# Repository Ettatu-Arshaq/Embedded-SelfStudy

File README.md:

# 🚀 Embedded Systems Self-Study Journey

**Author:** Muhammad Arshaq (Ettatu-Arshaq)
**Goal:** Become job-ready for Embedded Systems roles by **December 2025** through self-study and hands-on projects.

---

## 📅 Roadmap Overview

This repository documents my entire **Embedded Systems self-study path** — from C programming to IoT and RTOS — built phase by phase with practical examples and mini-projects.

---

## 📂 Phase 1: C Programming & Linux Fundamentals

* ✅ Variables, loops, functions, arrays, strings
* ✅ Structures, file handling, pointers, DMA

### 📂 Workouts (Practice Programs)

Located in [`Phase1_C/Workouts/C`](./Phase1_C/Workouts/C)

#### 🔗 Quick Links

* **Matrix Operations**

  * [Add two matrices](./Phase1_C/Workouts/C/Add_matrix.c)
  * [Add two matrices (function-based)](./Phase1_C/Workouts/C/Add_matrix_fn.c)
* **Arrays & Statistics**

  * [Average of Array](./Phase1_C/Workouts/C/Avg%20of%20Array_1_9-6-25.c)
  * [Largest Element in Array](./Phase1_C/Workouts/C/Largest_Element_inarray.c)
  * [Standard Deviation](./Phase1_C/Workouts/C/Standard_Deviation.c)
* **Strings**

  * [Count String Function](./Phase1_C/Workouts/C/Count_stringfn.c)
  * [Character Frequency](./Phase1_C/Workouts/C/char_freq.c)
  * [Remove Substring](./Phase1_C/Workouts/C/strremove.c)
  * [Reverse String](./Phase1_C/Workouts/C/strrev.c)
  * [String Sort Hierarchy](./Phase1_C/Workouts/C/strsorthirerarcy.c)
* **File Handling**

  * [File Handling Basics](./Phase1_C/Workouts/C/File.c)
  * [Binary File Write](./Phase1_C/Workouts/C/File_bin_wr.c)
  * [Text → Binary: Entry.txt](./Phase1_C/Workouts/C/txtorbin/Entry.txt)
  * [Text → Binary: Student.txt](./Phase1_C/Workouts/C/txtorbin/Student.txt)
* **Pointers & Memory**

  * [Dynamic Memory Example](./Phase1_C/Workouts/C/memory.c)
  * [Pointer Demo](./Phase1_C/Workouts/C/pointer.c)
  * [Pointer Basics](./Phase1_C/Workouts/C/pointer_basics.c)
  * [Pointer Arithmetic](./Phase1_C/Workouts/C/pointer_arthematic.c)
  * [Print Address](./Phase1_C/Workouts/C/print_adress.c)
* **Misc Examples**

  * [Example Program](./Phase1_C/Workouts/C/example.c)
  * [Temp Runner](./Phase1_C/Workouts/C/tempCodeRunnerFile.c)
  * [Extern Keyword Example](./Phase1_C/Workouts/C/ext.c)
  * [Main Function Demo](./Phase1_C/Workouts/C/main.c)

---

### 📂 Mini Projects

* [`Student Record Manager`](./Phase1_C/StudentManager)

  * C program using structures and binary file handling
  * Add, search, delete, and view student records
  * Demonstrates persistence with `.bin` files

* [`Student Manager Dynamic`](./Phase1_C/StudentManager/Student_Dynamic.c)

  * Enhanced Student Manager using dynamic memory allocation

* [`Bitwise Demo`](./Phase1_C/Bitwise_Demo)

  * Practice on bitwise operators and manipulation in C
  * Includes [Bitwise_Demo.c](./Phase1_C/Bitwise_Demo/Bitwise_Demo.c) with explanations

* [`LED Blinker`](./Phase1_C/LED_Blinker)

  * A simple LED blinking project (Code::Blocks project)
  * Includes [main.c](./Phase1_C/LED_Blinker/main.c), configs, and layout files

---

## 📂 Phase 2: Microcontroller Programming (PIC16F1519)

Located in [`Phase2_MC_PIC16F1519`](./Phase2_MC_PIC16F1519)

### 📁 Projects

* [LED 7-Segment Display](./Phase2_MC_PIC16F1519/LED_7Segment.X)
* [Multi-LED Patterns (GPIO only)](./Phase2_MC_PIC16F1519/Multi-LED%20Patterns%20%28GPIO%20only%29.X)
* [Timer Tick 2 LED](./Phase2_MC_PIC16F1519/Timer_tick_2_LED.X)

### 📂 Workouts

* [ADC LED Blink](./Phase2_MC_PIC16F1519/Workouts/ADC_LED_BLINK.X)
* [ADC Potentiometer Poll](./Phase2_MC_PIC16F1519/Workouts/ADC_Potentiometer_poll.X)
* [ADC Reader UART Select](./Phase2_MC_PIC16F1519/Workouts/ADC_READER_UART_SELECT.X)
* [Blink LED](./Phase2_MC_PIC16F1519/Workouts/BLINK_led.X)
* [Counter using Timer](./Phase2_MC_PIC16F1519/Workouts/Counter/Counter_using_timer.X)
* [EEPROM PIC](./Phase2_MC_PIC16F1519/Workouts/EEPROM_PIC.X)
* [EEPROM UART PIC](./Phase2_MC_PIC16F1519/Workouts/EEPROM_UART_PIC.X)
* [LED GPIO Trigger](./Phase2_MC_PIC16F1519/Workouts/LED_GPIO_TRIG.X)
* [PIC SPI Master](./Phase2_MC_PIC16F1519/Workouts/PIC_SPI.X)
* [PIC SPI Slave](./Phase2_MC_PIC16F1519/Workouts/PIC_SPI_SLAVE.X)
* [PWM Hardware](./Phase2_MC_PIC16F1519/Workouts/PWM.X)
* [PWM Software](./Phase2_MC_PIC16F1519/Workouts/PWM_soft.X)
* [Timer0](./Phase2_MC_PIC16F1519/Workouts/Time0)
* [Timer1](./Phase2_MC_PIC16F1519/Workouts/Timer1.X)
* [Timer2](./Phase2_MC_PIC16F1519/Workouts/Timer2.X)
* [UART Rx Program](./Phase2_MC_PIC16F1519/Workouts/UART_Rx_PGM.X)

---

## 📂 Phase 3: STM32 & RTOS (In Progress)

Located in [`Phase3_STM32`](./Phase3_STM32)

### 🧠 Topics Covered

* Bare-metal driver development (GPIO, RCC, Registers)
* STM32 architecture (ARM Cortex-M)
* Interrupts, Timers, PWM
* UART, SPI communication
* Introduction to FreeRTOS (Tasks, Queues, Semaphores)

---

### 📁 Projects

* [FreeRTOS Button Event System](./Phase3_STM32/RTOS_MiniProject/)
* [STM32 Smart Control System)](./Phase3_STM32/UART_Based_Smart_Control_System_ISR/)

---

### 📂 Workouts

* [UART Based Smart Control System](./Phase3_STM32/Workouts/UART_Based_Smart_Control_System/)
* [SYSTICK](./Phase3_STM32/Workouts/SYSTICK_/)
* [TIM2 Interrupt](./Phase3_STM32/Workouts/TIM2_INT/)
* [TIM2 LED Blink](./Phase3_STM32/Workouts/TIM2_LEDBlink/)
* [RTOS Soft Timer](./Phase3_STM32/Workouts/RTOS_SoftTimer/)
* [SYSClock Check](./Phase3_STM32/Workouts/SYSClock_Check/)
* [RTOS Semaphore](./Phase3_STM32/Workouts/RTOS_Semaphore/)
* [RTOS Queue TxRx](./Phase3_STM32/Workouts/RTOS_Queue_TxRx/)
* [RTOS Queue ISR](./Phase3_STM32/Workouts/RTOS_Queue_ISR/)
* [RTOS Queue](./Phase3_STM32/Workouts/RTOS_Queue/)
* [RTOS Mutex](./Phase3_STM32/Workouts/RTOS_Mutex/)
* [RTOS LED](./Phase3_STM32/Workouts/RTOS_LED/)
* [RTOS Heap](./Phase3_STM32/Workouts/RTOS_Heap/)
* [LED Blink Pattern](./Phase3_STM32/Workouts/LED_Blink_Patt/)
* [PWM](./Phase3_STM32/Workouts/PWM/)
* [EXTI](./Phase3_STM32/Workouts/EXTI/)
* [EXTI Debounce](./Phase3_STM32/Workouts/EXTI-debounce/)
* [LED Blink](./Phase3_STM32/Workouts/LED_Blink/)
* [LED Blink CMSIS](./Phase3_STM32/Workouts/LED_Blink_CMSIS/)
* [ADC DMA Channel](./Phase3_STM32/Workouts/ADC+dma_Ch/)
* [Clock 1](./Phase3_STM32/Workouts/Clock_1/)
* [Clock HSE PLL](./Phase3_STM32/Workouts/Clock_HSE_PLL/)
* [Clock PLL Speed](./Phase3_STM32/Workouts/Clock_pll_speed/)
* [ADC](./Phase3_STM32/Workouts/ADC/)
* [ADC DMA](./Phase3_STM32/Workouts/ADC+dma/)
---

## 📂 Phase 4: IoT & Cloud Integration *(Upcoming)*

* ESP32 with MQTT & Blynk
* Cloud dashboard (Firebase)

---

## 📂 Phase 5: Final Project & Job Preparation *(Upcoming)*

* Internship-level embedded project
* Resume, GitHub portfolio, LinkedIn updates

---

## 📦 Repository Structure

Embedded-SelfStudy/
├── Phase1_C/
│ ├── Workouts/
│ │ └── C/ # Practice programs
│ ├── Bitwise_Demo/ # Bitwise operator practice
│ ├── StudentManager/ # Mini Projects
│ └── LED_Blinker/ # LED Blinker project
├── Phase2_MC_PIC16F1519/
│ ├── Workouts/
│ ├── LED_7Segment.X/
│ └── Multi-LED Patterns (GPIO only).X/
└── ...
├── Phase3_RTOS/ # Will be added later
└── ...

---

## 🛠 Tools & Platforms

* **Languages:** C, Python
* **Boards:** ESP32, STM32 Nucleo, Raspberry Pi
* **IDE/Tools:** Arduino IDE, PlatformIO, STM32CubeIDE, Proteus, Code::Blocks
* **OS:** Windows + Linux basics

---

## 📢 Connect

* [GitHub Profile](https://github.com/Ettatu-Arshaq)
* [LinkedIn](https://www.linkedin.com/in/muhammad-arshaq-0b7455237/)

---

📅 **Started:** August 2025
💡 **Goal:** Complete all phases & projects by **December 2025**

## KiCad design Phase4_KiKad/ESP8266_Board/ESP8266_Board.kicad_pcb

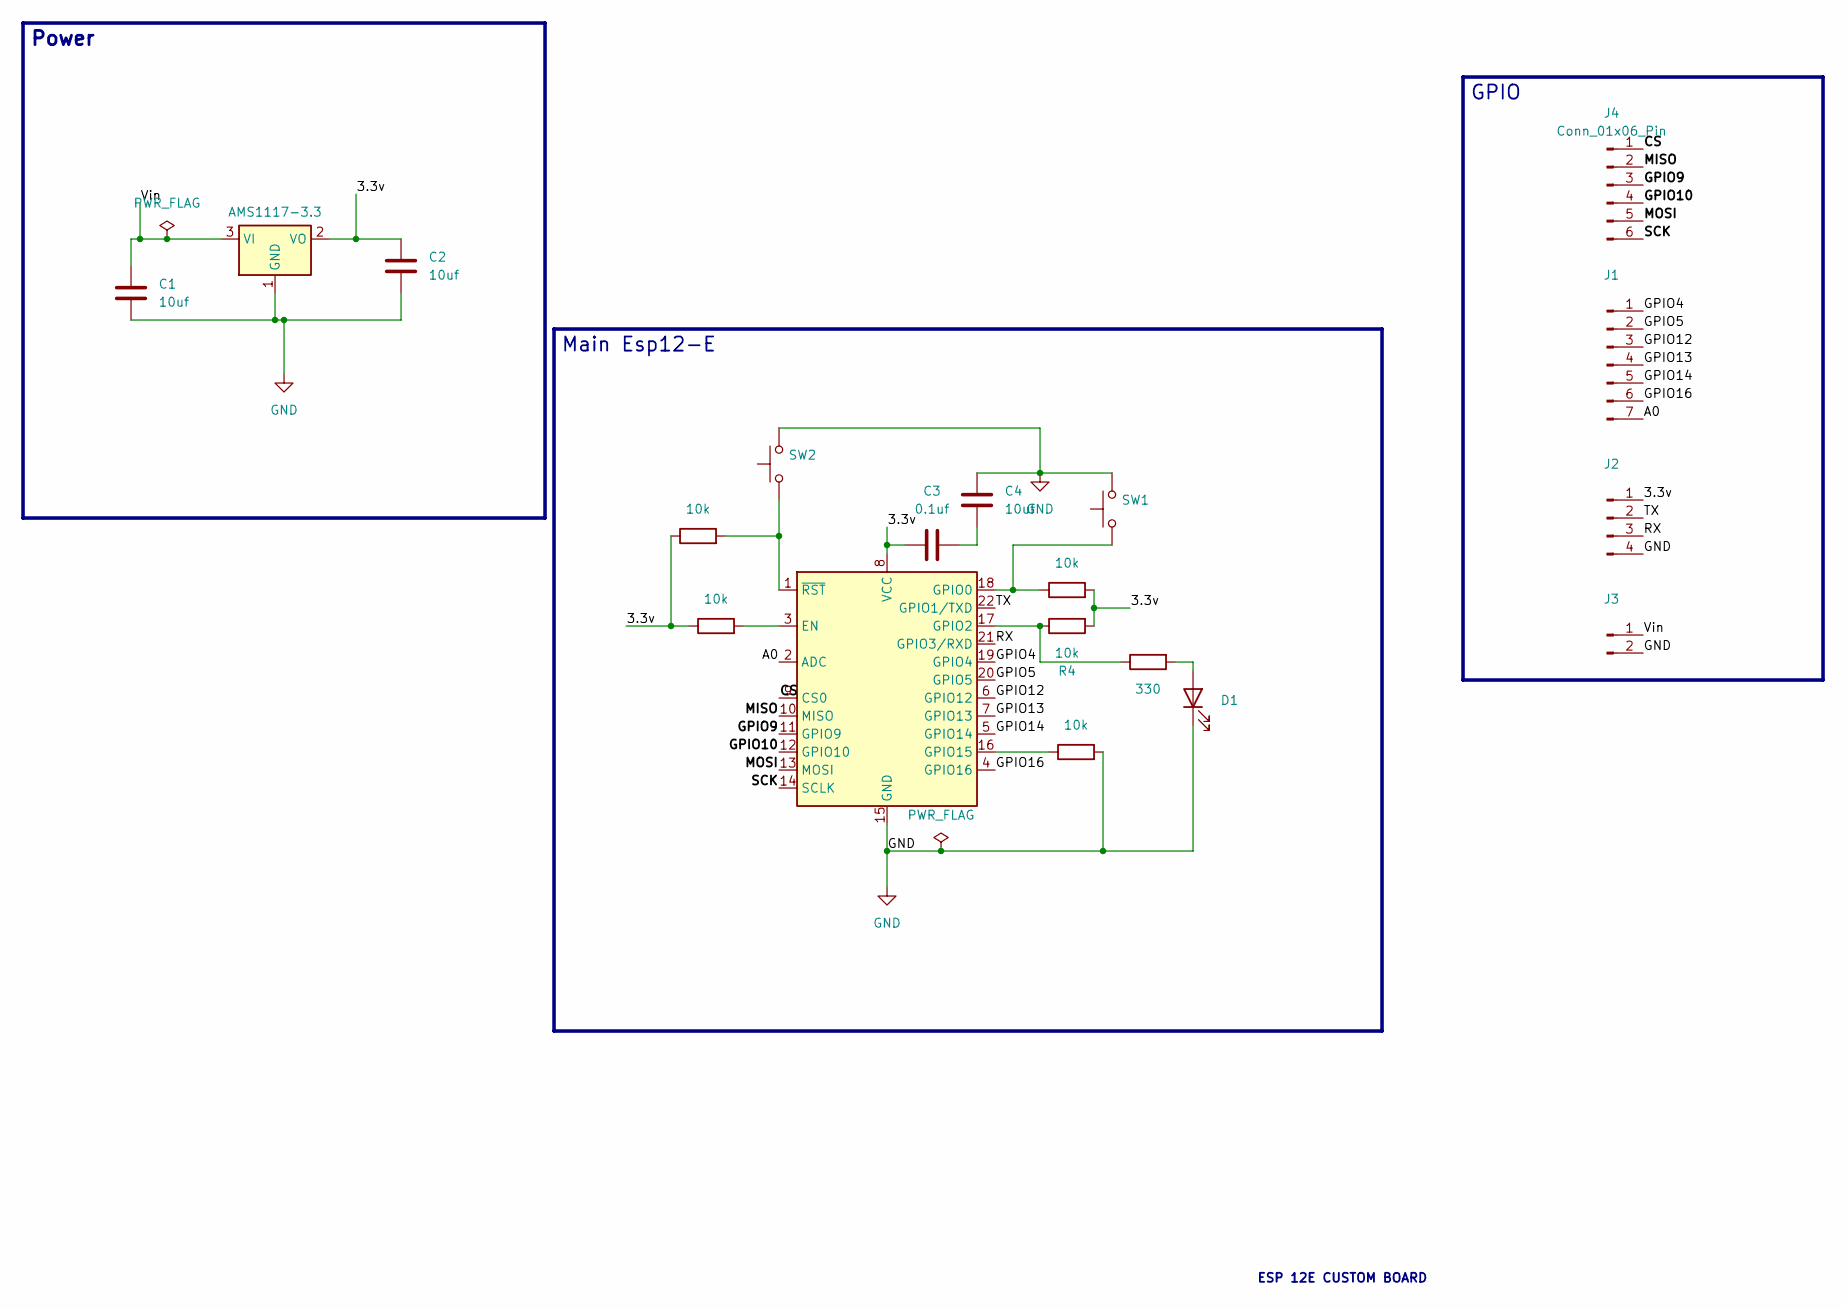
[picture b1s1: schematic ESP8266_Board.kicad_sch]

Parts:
C1, C2, C4: 10uf; C_0805_2012Metric_Pad1.18x1.45mm_HandSolder
C3: 0.1uf; C_0603_1608Metric_Pad1.08x0.95mm_HandSolder
D1: LED; LED_0603_1608Metric
J1: Conn_01x07_Pin; PinHeader_1x07_P1.00mm_Vertical
J2: Conn_01x04_Pin; PinHeader_1x04_P1.00mm_Vertical
J3: Conn_01x02_Pin; PinHeader_1x02_P1.00mm_Vertical
J4: Conn_01x06_Pin; PinHeader_1x06_P1.00mm_Vertical
R2, R3: 10k; R_0815_2038Metric
R4, R5, R6: 10k; R_0805_2012Metric
R7: 330; R_1210_3225Metric
SW1, SW2: SW_Push; SW_Push_1P1T_NO_CK_KMR2
U1: ESP-12E
U2: AMS1117-3.3; SOT-223-3_TabPin2

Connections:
/3.3v: C2.1, C3.1, J2.1, R2.1, R3.2, R4.2, R6.1, U1.8 (VCC), U2.2 (VO)
/A0: J1.7, U1.2 (ADC)
/CS: J4.1, U1.9 (CS0)
/GPIO4: J1.1, U1.19 (GPIO4)
/GPIO5: J1.2, U1.20 (GPIO5)
/GPIO9: J4.3, U1.11 (GPIO9)
/GPIO10: J4.4, U1.12 (GPIO10)
/GPIO12: J1.3, U1.6 (GPIO12)
/GPIO13: J1.4, U1.7 (GPIO13)
/GPIO14: J1.5, U1.5 (GPIO14)
/GPIO16: J1.6, U1.4 (GPIO16)
/MISO: J4.2, U1.10 (MISO)
/MOSI: J4.5, U1.13 (MOSI)
/RX: J2.3, U1.21 (GPIO3/RXD)
/SCK: J4.6, U1.14 (SCLK)
/TX: J2.2, U1.22 (GPIO1/TXD)
/Vin: C1.1, J3.1, U2.3 (VI)
GND: C1.2, C2.2, C4.1, D1.1 (K), J2.4, J3.2, R5.2, SW1.2, SW2.2, U1.15 (GND), U2.1 (GND)
unnamed: C3.2, C4.2
unnamed: D1.2 (A), R7.2
unnamed: R2.2, U1.3 (EN)
unnamed: R3.1, SW1.1, U1.18 (GPIO0)
unnamed: R4.1, R7.1, U1.17 (GPIO2)
unnamed: R5.1, U1.16 (GPIO15)
unnamed: R6.2, SW2.1, U1.1 (~RST)

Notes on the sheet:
ESP 12E CUSTOM BOARD
Power
GPIO
Main Esp12-E

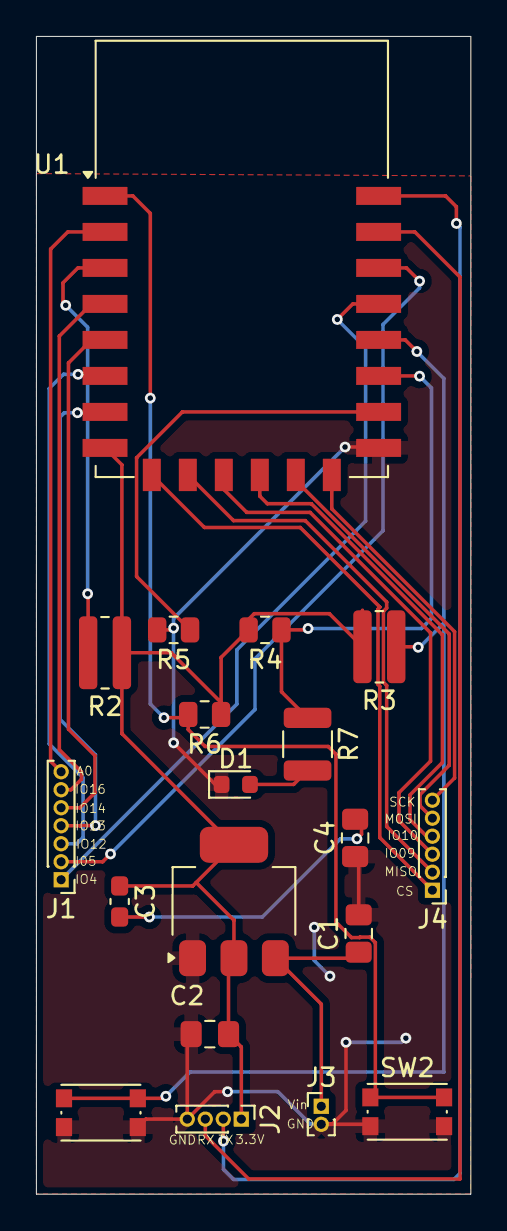
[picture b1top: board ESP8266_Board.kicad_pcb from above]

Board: 2 copper layers, 24.1 x 64.3 mm, 19 parts (0 on the bottom side), 25 nets.

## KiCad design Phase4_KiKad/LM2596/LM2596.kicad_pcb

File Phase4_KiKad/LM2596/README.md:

# ⚡ LM2596 Buck Converter – PCB Design (KiCad)

## 📌 Project Overview

This project is a **DC-DC Buck Converter PCB** designed using **KiCad**, based on the widely used **LM2596** switching regulator.

The circuit efficiently steps down a higher DC input voltage to a stable lower output voltage, making it ideal for embedded and IoT applications.

---

## ⚙️ Working Principle

The **LM2596** operates as a **switching regulator (buck converter)**:

1. Input DC voltage is applied through a barrel jack.
2. The IC switches internally at high frequency (~150 kHz).
3. Energy is stored in the inductor during ON time.
4. During OFF time, energy is released through the Schottky diode.
5. Output is filtered using capacitors to provide a stable DC voltage.
6. Feedback (FB pin) maintains constant output voltage.

---

## 🧩 Circuit Components

| Component | Description                   |
| --------- | ----------------------------- |
| U1        | LM2596S-ADJ Buck Converter IC |
| J3        | Barrel Jack (DC Input)        |
| C1        | Input Capacitor (680µF)       |
| L1        | Inductor (33µH)               |
| D1        | Schottky Diode (1N5822)       |
| C2        | Output Capacitor (220µF)      |
| J2        | Output Connector              |
| PWR_FLAG  | Power indication              |
| GND       | Ground reference              |

---

## 🔌 Input / Output

### Input:

* Voltage: **7V – 35V DC** (typical)
* Connector: Barrel Jack

### Output:

* Adjustable DC Output (based on feedback network)
* Connector: 2-pin header

---

## 🎛️ Features

* High efficiency (up to ~90%)
* Wide input voltage range
* Adjustable output voltage
* Compact and robust design
* Suitable for embedded systems power supply

---

## 🛠️ Design Tools

* **KiCad** (Schematic + PCB)

---

## 📷 PCB

---

## 🚀 Applications

* Power supply for **STM32 / Arduino / ESP modules**
* Battery-powered systems
* IoT devices
* Robotics projects

---

## ⚠️ Important Design Notes

* Use **low ESR capacitors** for stability
* Keep **switching loop (IC + diode + inductor)** as short as possible in PCB
* Use **thick traces** for high current paths
* Proper grounding is critical for noise reduction

---

## 🔧 Future Improvements

* Add output voltage adjustment potentiometer (feedback divider)
* Include heatsink provision for high load
* Add LED power indicator
* Add reverse polarity protection

---

## 🧠 Learning Outcomes

* Understanding **switching regulators**
* Buck converter design fundamentals
* Power electronics basics
* PCB layout considerations for power circuits

---

## 🔗 Author

**Muhammad Arshaq**
Embedded Systems & IoT Enthusiast

---

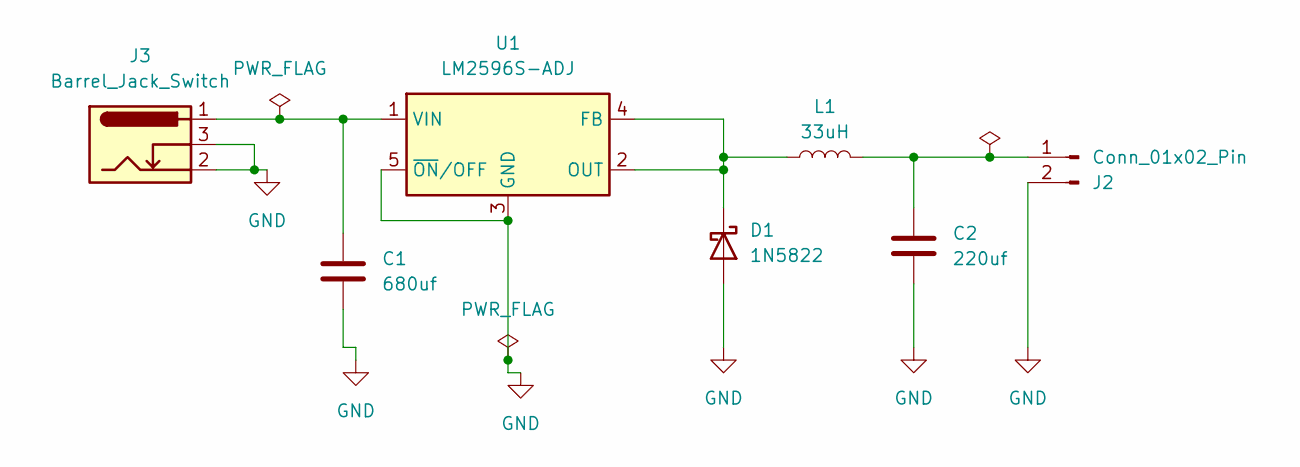
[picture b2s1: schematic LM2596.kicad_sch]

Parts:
C1: 680uf; C_0201_0603Metric
C2: 220uf; C_0201_0603Metric
D1: 1N5822; D_DO-201AD_P15.24mm_Horizontal
J2: Conn_01x02_Pin; JWT_A3963_1x02_P3.96mm_Vertical
J3: Barrel_Jack_Switch; BarrelJack_Kycon_KLDX-0202-xC_Horizontal
L1: 33uH; L_6.3x6.3_H3
U1: LM2596S-ADJ; TO-263-5_TabPin3

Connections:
GND: C1.2, C2.2, D1.2 (A), J2.2, J3.2, J3.3, U1.3 (GND), U1.5 (~ON/OFF)
unnamed: D1.1 (K), L1.1, U1.2 (OUT), U1.4 (FB)
unnamed: C2.1, J2.1, L1.2
unnamed: C1.1, J3.1, U1.1 (VIN)

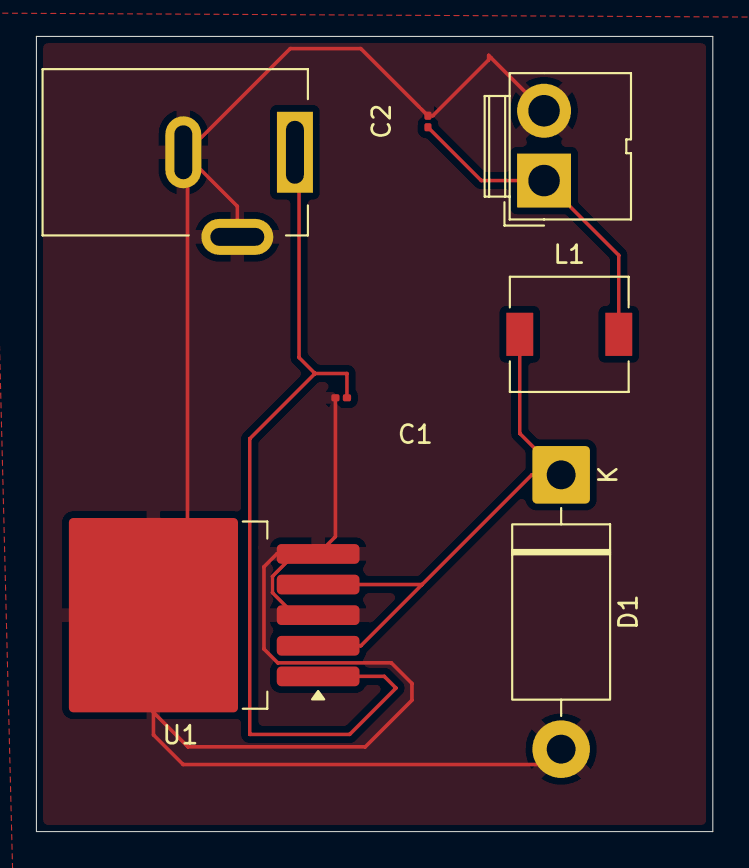
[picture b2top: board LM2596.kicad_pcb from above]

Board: 2 copper layers, 37.6 x 44.2 mm, 7 parts (0 on the bottom side), 4 nets.

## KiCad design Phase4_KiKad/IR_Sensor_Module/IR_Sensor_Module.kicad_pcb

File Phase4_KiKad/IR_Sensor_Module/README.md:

# 📡 IR Sensor Module – PCB Design (KiCad)

## 📌 Project Overview

This project is a custom-designed **Infrared (IR) Sensor Module PCB** created using **KiCad**. The module detects objects using IR transmission and reception, processes the signal using a comparator (op-amp), and provides a digital output.

This design is suitable for:

* Obstacle detection robots 🤖
* Line-following systems
* Proximity sensing applications

---

## ⚙️ Working Principle

The module works based on **IR reflection**:

1. **IR LED (Transmitter)** emits infrared light.
2. When an object is present, IR light is reflected back.
3. **Photodiode (Receiver)** detects the reflected IR signal.
4. The signal is converted into voltage and passed to an **Op-Amp Comparator**.
5. Comparator compares signal with a reference voltage (set via potentiometer).
6. Output is:

   * **HIGH** → Object detected
   * **LOW** → No object

---

## 🧩 Circuit Components

| Component | Description                          |
| --------- | ------------------------------------ |
| D3        | IR Transmitter LED                   |
| D2        | IR Receiver (Photodiode)             |
| U1A       | Op-Amp Comparator                    |
| R1        | Current limiting resistor for IR LED |
| R2        | Pull-down resistor                   |
| R3        | Output LED resistor                  |
| R4        | Potentiometer (Sensitivity control)  |
| D1        | Output Indicator LED                 |
| J1        | Output Header Pins                   |
| PWR_FLAG  | Power indication                     |
| GND_FLAG  | Ground reference                     |

---

## 🔌 Pin Configuration (J1)

| Pin | Function  |
| --- | --------- |
| 1   | VCC (+5V) |
| 2   | OUTPUT    |
| 3   | GND       |

---

## 🎛️ Features

* Adjustable sensitivity using potentiometer
* On-board output LED indicator
* Compact PCB design
* Simple digital output interface
* Easy integration with microcontrollers (STM32, Arduino, etc.)

---

## 🛠️ Design Tools

* **KiCad** (Schematic + PCB Design)

---

## 📷 PCB

---

## 🚀 Applications

* Line follower robot
* Obstacle avoidance robot
* Object counting systems
* Automation projects

---

## 📈 Future Improvements

* Add noise filtering capacitor
* Use LM393 comparator for better stability
* Add mounting holes for mechanical support
* Improve IR shielding for accuracy

---

## 🧠 Learning Outcomes

* Understanding IR sensing principles
* Comparator circuit design
* Analog-to-digital signal conversion
* PCB design workflow in KiCad

---

## 🔗 Author

**Muhammad Arshaq**
Embedded Systems Enthusiast

---

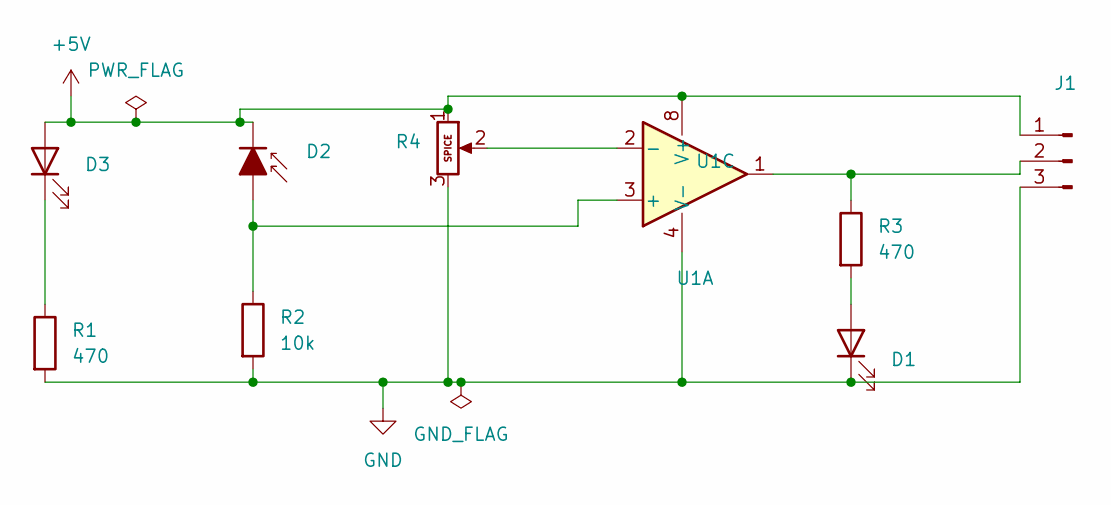
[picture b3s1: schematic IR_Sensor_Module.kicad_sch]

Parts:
D1, D3: IR26-21C_L110_TR8; LED_1206_3216Metric
D2: D_Photo_Filled; LED_1206_3216Metric
J1: Conn_01x03_Pin; PinHeader_1x03_P1.00mm_Vertical
R1: 470; R_0603_1608Metric_Pad0.98x0.95mm_HandSolder
R2: 10k; R_0805_2012Metric_Pad1.20x1.40mm_HandSolder
R3: 470; R_0805_2012Metric_Pad1.20x1.40mm_HandSolder
R4: 10k; Potentiometer_ACP_CA14-VSMD_Vertical
U1: LM358; SOIC-8_5.3x6.2mm_P1.27mm

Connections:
+5V: D2.1 (K), D3.2 (A), J1.1, R4.1, U1.8 (V+)
GND: D1.1 (K), J1.3, R1.2, R2.2, R4.3, U1.4 (V-)
unnamed: D1.2 (A), R3.2
unnamed: D2.2 (A), R2.1, U1.3 (+)
unnamed: D3.1 (K), R1.1
unnamed: J1.2, R3.1, U1.1
unnamed: R4.2, U1.2 (-)

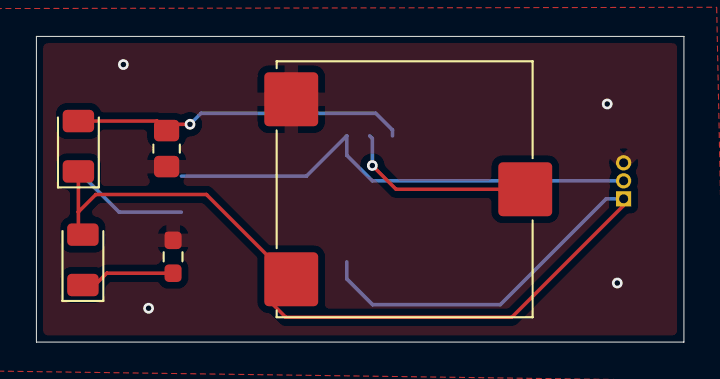
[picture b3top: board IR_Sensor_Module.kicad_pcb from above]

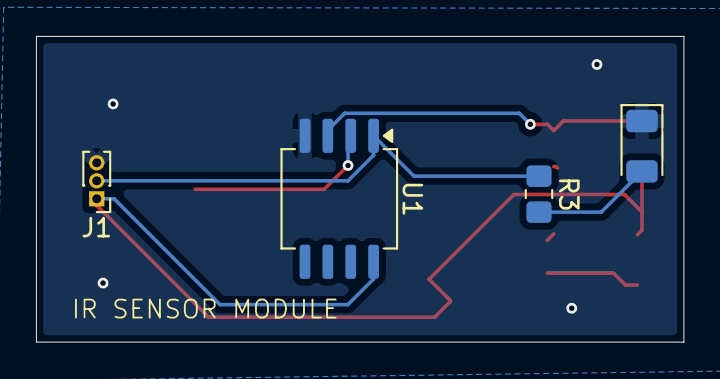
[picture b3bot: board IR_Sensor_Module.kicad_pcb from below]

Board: 2 copper layers, 36.0 x 17.0 mm, 9 parts (4 on the bottom side), 7 nets.

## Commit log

2025-08-09 Phase 1: Added Student Record Manager (C + File Handling)
2025-08-09 Added root-level README with roadmap and repo overview
2025-08-09 Move .gitignore to root and clean tracked files
2025-08-24 Reorganized repo: moved all files under embedded/, added workouts folder
2025-10-31 Added .gitignore for MPLAB X and Proteus projects
2026-04-17 Updated README and added Phase 3 content
2026-04-17 Removed build files and added .gitignore
2026-04-17 Removed build files and updated .gitignore
2026-04-17 Update Phase 3 with STM32 and RTOS work
2026-04-18 Reorganized repo: moved workouts under phase1 in embedded_self_study
2026-04-18 Readme fix 7 seg
2026-04-24 your update
2026-04-24 Removed embedded git repo (.history) and updated gitignore
2026-05-06 ESP8266 Kikad added
